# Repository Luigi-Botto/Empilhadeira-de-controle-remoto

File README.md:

# Carrinho de Controle Remoto BLE - Raspberry Pi Pico
Luigi Lauand Botto - 23.01066-5
Luigi de Menezes Collesi - 23.00625-0
Enzo Pistori Fontenelle de Oliveira - 23.00768-5

Este repositório contém os arquivos de hardware, firmware e documentação técnica para o desenvolvimento de um carrinho de controle remoto controlado via smartphone, projetado como parte da disciplina de Microcontroladores. O sistema utiliza o microcontrolador **Raspberry Pi Pico**, comunicação via **Bluetooth Low Energy (BLE)** e uma estrutura robusta montada sobre um chassi de **MDF** com placas de circuito impresso (PCI) customizadas.

---

## 📋 Sumário
1. [Visão Geral do Projeto](#-visão-geral-do-projeto)
2. [Arquitetura do Sistema](#-arquitetura-do-sistema)
3. [Especificações de Hardware](#-especificações-de-hardware)
4. [Mapeamento de Pinos (GPIO)](#-mapeamento-de-pinos-gpio)
5. [Evolução do Design Mecânico e PCI](#-evolução-do-design-mecânico-e-pci)
6. [Firmware e Protocolo de Comunicação](#-firmware-e-protocolo-de-comunicação)
7. [Estrutura do Repositório](#-estrutura-do-repositório)
8. [Orçamento do Projeto](#-orçamento-do-projeto)
9. [Como Executar o Projeto](#-como-executar-o-projeto)

---

## 🔍 Visão Geral do Projeto
O objetivo do projeto consiste na construção de um veículo terrestre de quatro rodas motrizes controlado remotamente através de um dispositivo móvel com sistema operacional **iOS**. 

A interface sem fio é estabelecida por meio do módulo Bluetooth BLE **HC-08**, responsável por realizar a ponte de comunicação entre o smartphone e o Raspberry Pi Pico. No ambiente iOS, é utilizado o aplicativo **BlackBLE** da RoboCore (adquirido por R$ 4,90), configurado para transmitir pacotes de dados baseados em caracteres simples em letras maiúsculas para o acionamento de direções e periféricos.

---

## 🛠 Arquitetura do Sistema
O fluxo elétrico e de sinais do protótipo segue uma topologia planejada para garantir níveis estáveis de tensão e proteção das portas lógicas do microcontrolador. Uma representação visual completa dessa estrutura está disponível no arquivo `diagrama_blocos.png` localizado na raiz do repositório.

### Fluxo de Potência e Conversão de Sinais:
1. **Fonte de Alimentação Primária:** O circuito é alimentado por uma bateria de lítio com tensão nominal de **7,2 Volts**.
2. **Regulação Buck (Step-Down):** A tensão da bateria é rebaixada e estabilizada por um conversor regulador **LM2596**, configurado para fornecer uma saída constante de **5V**.
3. **Alimentação da Lógica:** O Raspberry Pi Pico recebe energia de forma direta através do pino **VSYS**, utilizando a linha regulada de 5V vinda do step-down.
4. **Conversão de Nível Lógico:** Devido ao fato de o Raspberry Pi Pico operar nativamente com sinais lógicos de **3,3V** e a ponte H **L298N** requerer sinais de **5V** em suas linhas de controle para garantir o acionamento correto dos transistores, foi integrado um **Conversor de Nível Lógico Bidirecional**. O barramento de alta tensão (*High Voltage* - HV) deste módulo conversor é alimentado pelos 5V provenientes da saída do regulador step-down.

---

## ⚙️ Especificações de Hardware

Abaixo encontra-se a listagem detalhada dos principais componentes que integram o hardware do projeto:

| Componente | Função Principal | Especificação / Observação |
| :--- | :--- | :--- |
| **Raspberry Pi Pico** | Unidade de processamento central | Baseado no chip RP2040, operação a 3,3V |
| **Módulo HC-08** | Módulo de comunicação sem fio | Bluetooth Low Energy (BLE), interface serial UART |
| **Ponte H L298N** | Driver de potência para motores | Controle de até 2 canais independentes de corrente |
| **Motores DC (x4)** | Atuadores de tração mecânica | Ligados em paralelo (2 por canal da Ponte H) por lateral |
| **Conversor de Nível Lógico** | Interfaceamento de tensão de dados | Shifter bidirecional de sinal (3,3V para 5V) |
| **Módulo LM2596** | Regulador de tensão Step-Down | Conversor Buck DC-DC ajustado para saída estável de 5V |
| **Bateria de Lítio** | Armazenamento de energia | Tensão de operação de 7,2V |
| **LEDs de Alto Brilho (x2)** | Sistema de iluminação (Faróis) | Conectados em canais independentes (ON/OFF via app) |
| **Chassi Mecânico** | Estrutura física do veículo | Base em MDF com 3mm de espessura |

---

## 📌 Mapeamento de Pinos (GPIO)

As conexões físicas foram estruturadas no circuito impresso e inicializadas no firmware conforme o mapeamento a seguir:

| Periférico / Linha | Função do Pino | Pino no Raspberry Pi Pico | Configuração Digital | Detalhes Técnicos |
| :--- | :--- | :--- | :--- | :--- |
| **Interface UART0 (HC-08)** | Transmissão de Dados (TX) | **GPIO 16** | Saída (`Pin.OUT`) | Conectado diretamente ao RX do HC-08 |
| **Interface UART0 (HC-08)** | Recepção de Dados (RX) | **GPIO 17** | Entrada com Pull-Up (`Pin.IN, Pin.PULL_UP`) | Monitora dados vindos do TX do HC-08 |
| **Ponte H (Lado Esquerdo)** | Motor 1 - Terminal A | **GPIO 2** | Saída (`Pin.OUT`) | Sinal condicionado no Shifter para 5V |
| **Ponte H (Lado Esquerdo)** | Motor 1 - Terminal B | **GPIO 3** | Saída (`Pin.OUT`) | Sinal condicionado no Shifter para 5V |
| **Ponte H (Lado Direito)** | Motor 2 - Terminal A | **GPIO 4** | Saída (`Pin.OUT`) | Sinal condicionado no Shifter para 5V |
| **Ponte H (Lado Direito)** | Motor 2 - Terminal B | **GPIO 5** | Saída (`Pin.OUT`) | Sinal condicionado no Shifter para 5V |
| **Farol Esquerdo (D1)** | Acionamento do LED | **GPIO 28** | Saída (`Pin.OUT`) | Estado lógico controlado via comando BLE |
| **Farol Direito (D2)** | Acionamento do LED | **GPIO 27** | Saída (`Pin.OUT`) | Estado lógico controlado via comando BLE |

---

## 📐 Evolução do Design Mecânico e PCI

### Transição do Sistema de Esterço (Nota de Projeto)
O escopo inicial de engenharia contemplava um mecanismo de direção nas rodas dianteiras baseado no acionamento por um servo motor **MG996R**. A Placa de Circuito Impresso (PCI) foi desenvolvida, impressa e finalizada prevendo as trilhas de dados e alimentação dedicadas a este atuador.

Entretanto, nos ensaios mecânicos de integração, a geometria de esterço projetada apresentou falhas estruturais e travamentos na base de MDF. Como solução de contorno, a equipe optou pela substituição do modelo mecânico tradicional por uma configuração de **direção diferencial (skid-steer / tipo tanque)** utilizando quatro rodas motorizadas.

### Lógica de Curvas e Disposição dos Motores:
* **Conexão Mecânica:** Embora a ponte H L298N possua saídas de potência nominais para apenas dois motores, os quatro motores foram associados em pares paralelos. Os motores de uma mesma lateral pertencem ao mesmo canal de saída da ponte H (e não ao mesmo eixo transversal), permitindo o movimento conjunto de cada lado do veículo.
* **Operação de Curvas:** As manobras são feitas invertendo o sentido de rotação relativo entre as laterais:
  * **Giro à Esquerda:** Lateral direita movimenta-se para frente enquanto a lateral esquerda movimenta-se para trás.
  * **Giro à Direita:** Lateral esquerda movimenta-se para frente enquanto a lateral direita movimenta-se para trás.

*Nota de Design:* O circuito impresso finalizado (PCI) mantém as trilhas e o footprint originais destinados ao servo motor MG996R. Essa característica foi preservada como histórico de desenvolvimento e viabilidade de upgrades mecânicos futuros.

---

## 💻 Firmware e Protocolo de Comunicação

O ambiente lógico do sistema foi desenvolvido sob a linguagem **MicroPython**, utilizando o software **Thonny IDE** para gravação e depuração direta no microcontrolador.

### Protocolo Serial BLE:
A comunicação por Bluetooth baseia-se na escuta constante do barramento `UART(0)`. O aplicativo móvel *BlackBLE* envia strings contendo caracteres simples em **letras maiúsculas** de forma imediata à interação do usuário. O código realiza a leitura desses caracteres e altera as tabelas de verdade das portas lógicas associadas aos pinos `motor1_a`, `motor1_b`, `motor2_a` e `motor2_b` instantaneamente.

### Funcionamento dos Faróis:
Os dois LEDs de sinalização frontal (conectados às GPIOs 27 e 28) operam sob uma lógica assíncrona de alternância (*Toggle Button*). Um botão ON/OFF dedicado no painel do aplicativo envia os comandos específicos de ativação e desativação, mantendo os faróis ligados ou desligados independentemente do estado de translação dos motores.

---

## 📁 Estrutura do Repositório

* 📄 **`diagrama_blocos.png`**: Imagem esquemática detalhando a arquitetura interna e interconexão de blocos do circuito.
* 📄 **`Design_PCI.png`**: Desenho da placa para impressão.
* 📄 **`Esquematico_eletrico.png`**: Imagem esquemática do circuito no KiCad.
* 📄 **`main.py`** *(ou arquivo de código equivalente)*: Código-fonte em MicroPython que roda diretamente no Raspberry Pi Pico.
* 📄 **`README.md`**: Este arquivo de documentação técnica localizado na raiz do repositório.

---

## 💰 Orçamento do Projeto

Abaixo está a relação de custos dos componentes adquiridos para a montagem do protótipo:

| Componente / Material | Quantidade | Custo Estimado (R$) |
| :--- | :---: | :--- |
| Raspberry Pi Pico | 1 | 30,00 |
| Módulo Bluetooth HC-08 | 1 | 35,00 |
| Kit de Baterias (Pilhas Lítio) | 1 | 50,00 |
| Motores DC | 4 | 30,00 |
| Conversor de Nível Lógico | 1 | 25,00 |
| Ponte H L298N | 1 | 20,00 |
| Módulo Step-Down LM2596 | 1 | 7,50 |
| LEDs de Alto Brilho | 2 | 5,00 |
| Resistores | 2 | 0,20 |
| Placa de Circuito Impresso (PCI) | 1 | *Não determinado* |
| Chassi em MDF (3mm) | 1 | *Não determinado* |
| **Custo Total Parcial** | | **R$ 202,70** |

---

## 🚀 Como Executar o Projeto

1. **Validação da Alimentação:** Antes de conectar as saídas às portas digitais do Pico, verifique com um multímetro se a saída do módulo Step-Down LM2596 está ajustada estritamente para **5V** para não danificar o microcontrolador.
2. **Gravação do Firmware:** Abra a IDE Thonny, carregue o arquivo de código fonte, selecione o interpretador correto para o Raspberry Pi Pico e armazene o script diretamente na memória interna do dispositivo.
3. **Operação e Pareamento:** Inicialize a alimentação do circuito por meio da bateria de 7,2V. Abra o aplicativo **BlackBLE** em seu dispositivo iOS, realize o escaneamento físico e conecte-se ao módulo **HC-08**. Configure os botões gráficos para disparar os caracteres maiúsculos definidos para cada comando.

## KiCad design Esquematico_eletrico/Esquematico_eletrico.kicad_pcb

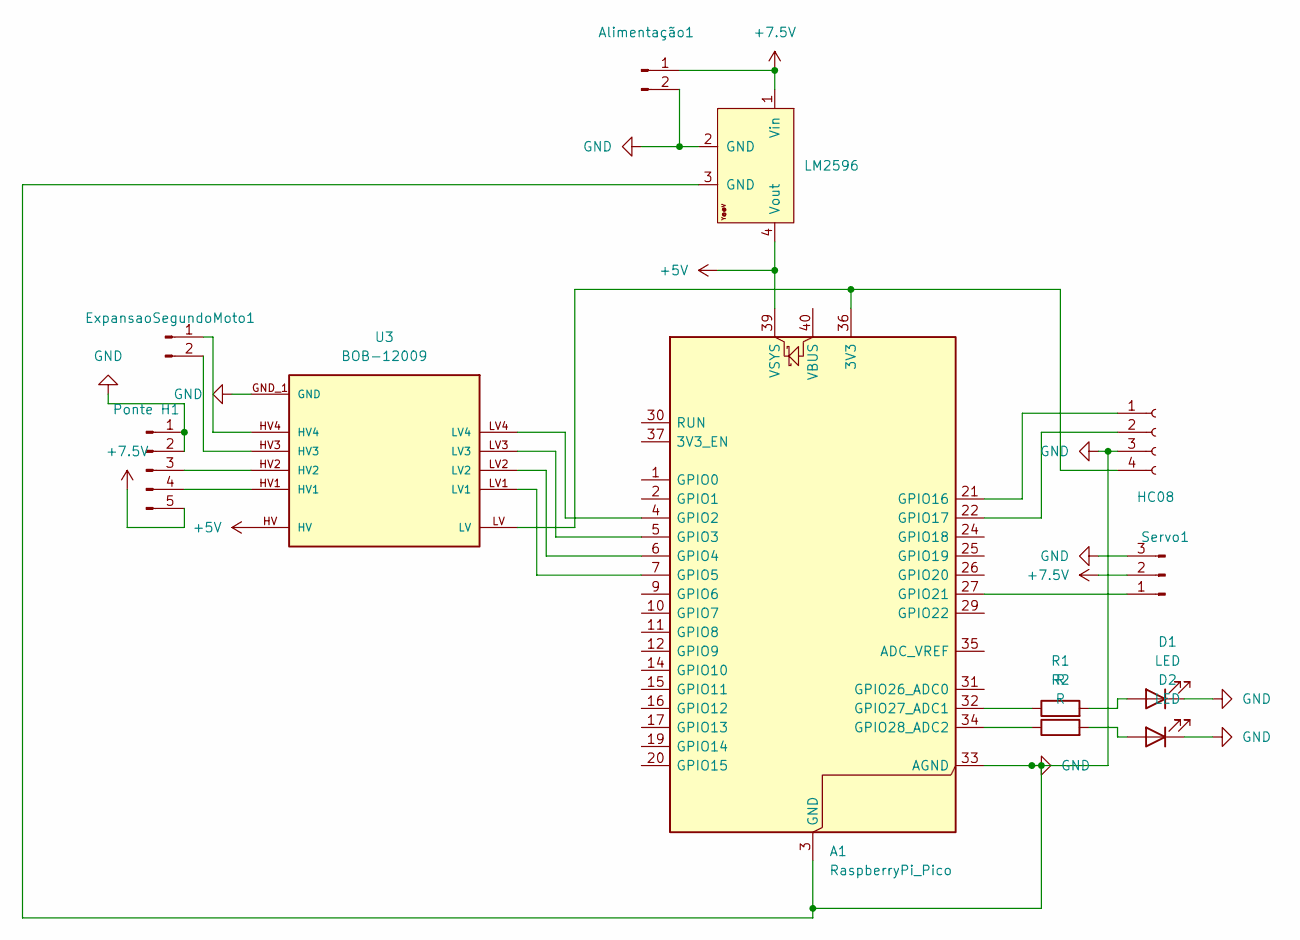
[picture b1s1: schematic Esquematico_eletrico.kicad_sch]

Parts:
A1: RaspberryPi_Pico; RaspberryPi_Pico_Common_Unspecified
Alimentação1: Conn_01x02_Pin; PinSocket_1x02_P2.54mm_Vertical
D1, D2: LED; LED_D5.0mm_FlatTop
ExpansaoSegundoMoto1: Conn_01x02_Pin; PinSocket_1x02_P2.54mm_Vertical
HC08: Conn_01x04_Socket; PinSocket_1x04_P2.54mm_Vertical
Ponte H1: Conn_01x05_Pin; PinSocket_1x05_P2.54mm_Vertical
R1, R2: R; R_Axial_DIN0207_L6.3mm_D2.5mm_P10.16mm_Horizontal
Servo1: Conn_01x03_Pin; PinHeader_1x03_P2.54mm_Vertical
U2: LM2596; YAAJ_DCDC_StepDown_LM2596
U3: BOB-12009; CONV_BOB-12009; PARTREV 01

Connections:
+5V: A1.39 (VSYS), U2.4 (Vout), U3.HV
+7.5V: Alimentação1.1, Ponte H1.5, Servo1.2, U2.1 (Vin)
GND: A1.3 (GND), A1.8 (GND), A1.13 (GND), A1.18 (GND), A1.23 (GND), A1.28 (GND), A1.33 (AGND), A1.38 (GND), Alimentação1.2, D1.1 (K), D2.1 (K), HC08.3, Ponte H1.1, Ponte H1.2, Servo1.3, U2.2 (GND), U2.3 (GND), U3.GND_1 (GND), U3.GND_2 (GND)
unnamed: A1.36 (3V3), HC08.4, U3.LV
unnamed: A1.4 (GPIO2), U3.LV4
unnamed: A1.5 (GPIO3), U3.LV3
unnamed: A1.6 (GPIO4), U3.LV2
unnamed: A1.7 (GPIO5), U3.LV1
unnamed: A1.21 (GPIO16), HC08.1
unnamed: A1.22 (GPIO17), HC08.2
unnamed: A1.27 (GPIO21), Servo1.1
unnamed: A1.32 (GPIO27_ADC1), R1.1
unnamed: A1.34 (GPIO28_ADC2), R2.1
unnamed: D1.2 (A), R1.2
unnamed: D2.2 (A), R2.2
unnamed: ExpansaoSegundoMoto1.1, U3.HV4
unnamed: ExpansaoSegundoMoto1.2, U3.HV3
unnamed: Ponte H1.3, U3.HV2
unnamed: Ponte H1.4, U3.HV1

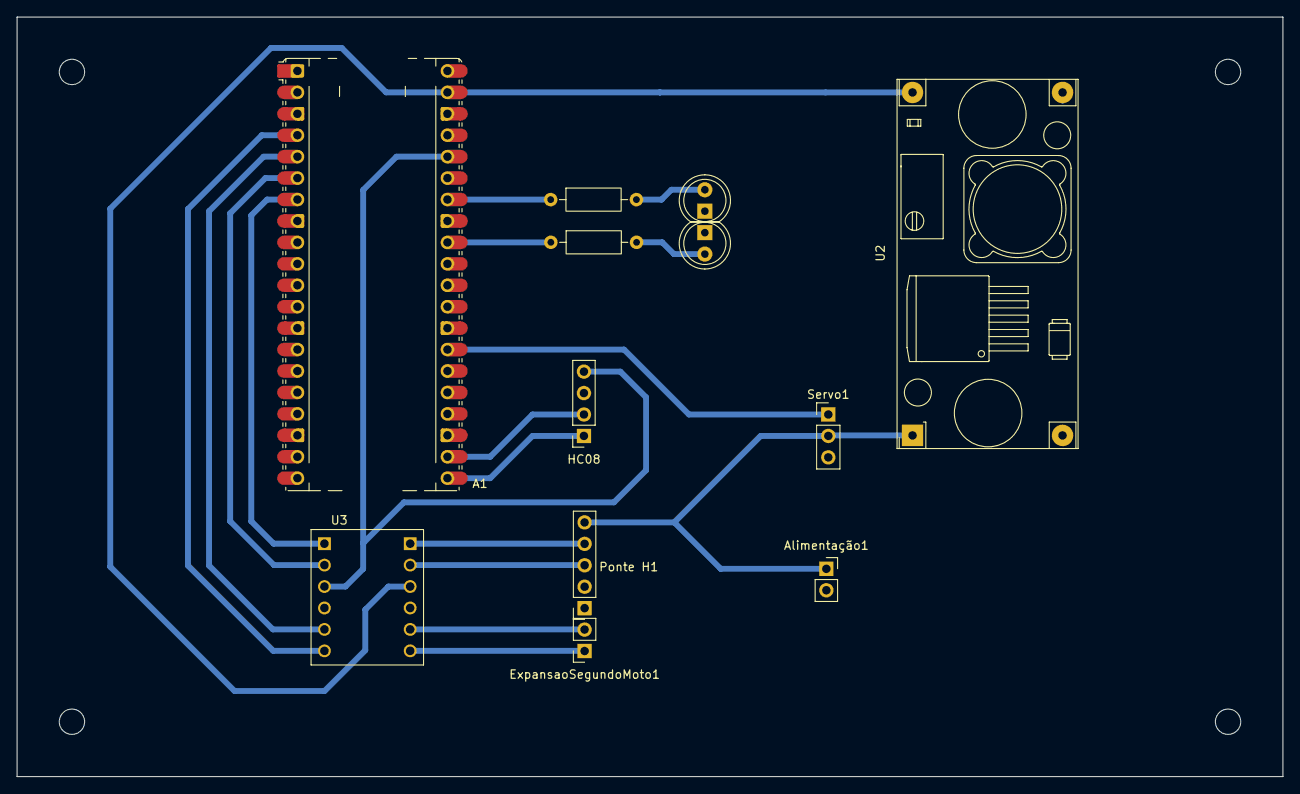
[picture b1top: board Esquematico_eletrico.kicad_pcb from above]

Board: 2 copper layers, 150.0 x 90.0 mm, 12 parts (0 on the bottom side), 19 nets.

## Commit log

2026-03-24 Primeiro commit: Diagrama de blocos
2026-06-03 Documentação
2026-06-03 atualizacao
2026-06-03 Mudancças md
2026-06-03 codigo
2026-06-03 edicao 2
2026-06-03 Ediçao final documentação
2026-06-03 Membros no readme
2026-06-03 fotos do projeto
2026-06-03 Fotos corretas e o video
